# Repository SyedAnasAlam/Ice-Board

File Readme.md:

# Ice Board 
Ice Board is a FPGA development board containing the ICE40HX4k from Lattice.  
## Parts
- Lattice ICE40HX4K FPGA
- W25X20CL 2Mbit SPI Flash for storing configuration bitstream (104MHz)
- USB-C for configuring the FPGA using [IceBoard Programmer](https://github.com/SyedAnasAlam/IceBoard-Programmer) 
    - Also has option for programming the flash with a external device though breakout headers
- Requires 5V supply which can be supplied from either USB port or barrel jack (selectable with a header)
- FTDI4222 for USB to SPI conversion
- 64 x IO pins

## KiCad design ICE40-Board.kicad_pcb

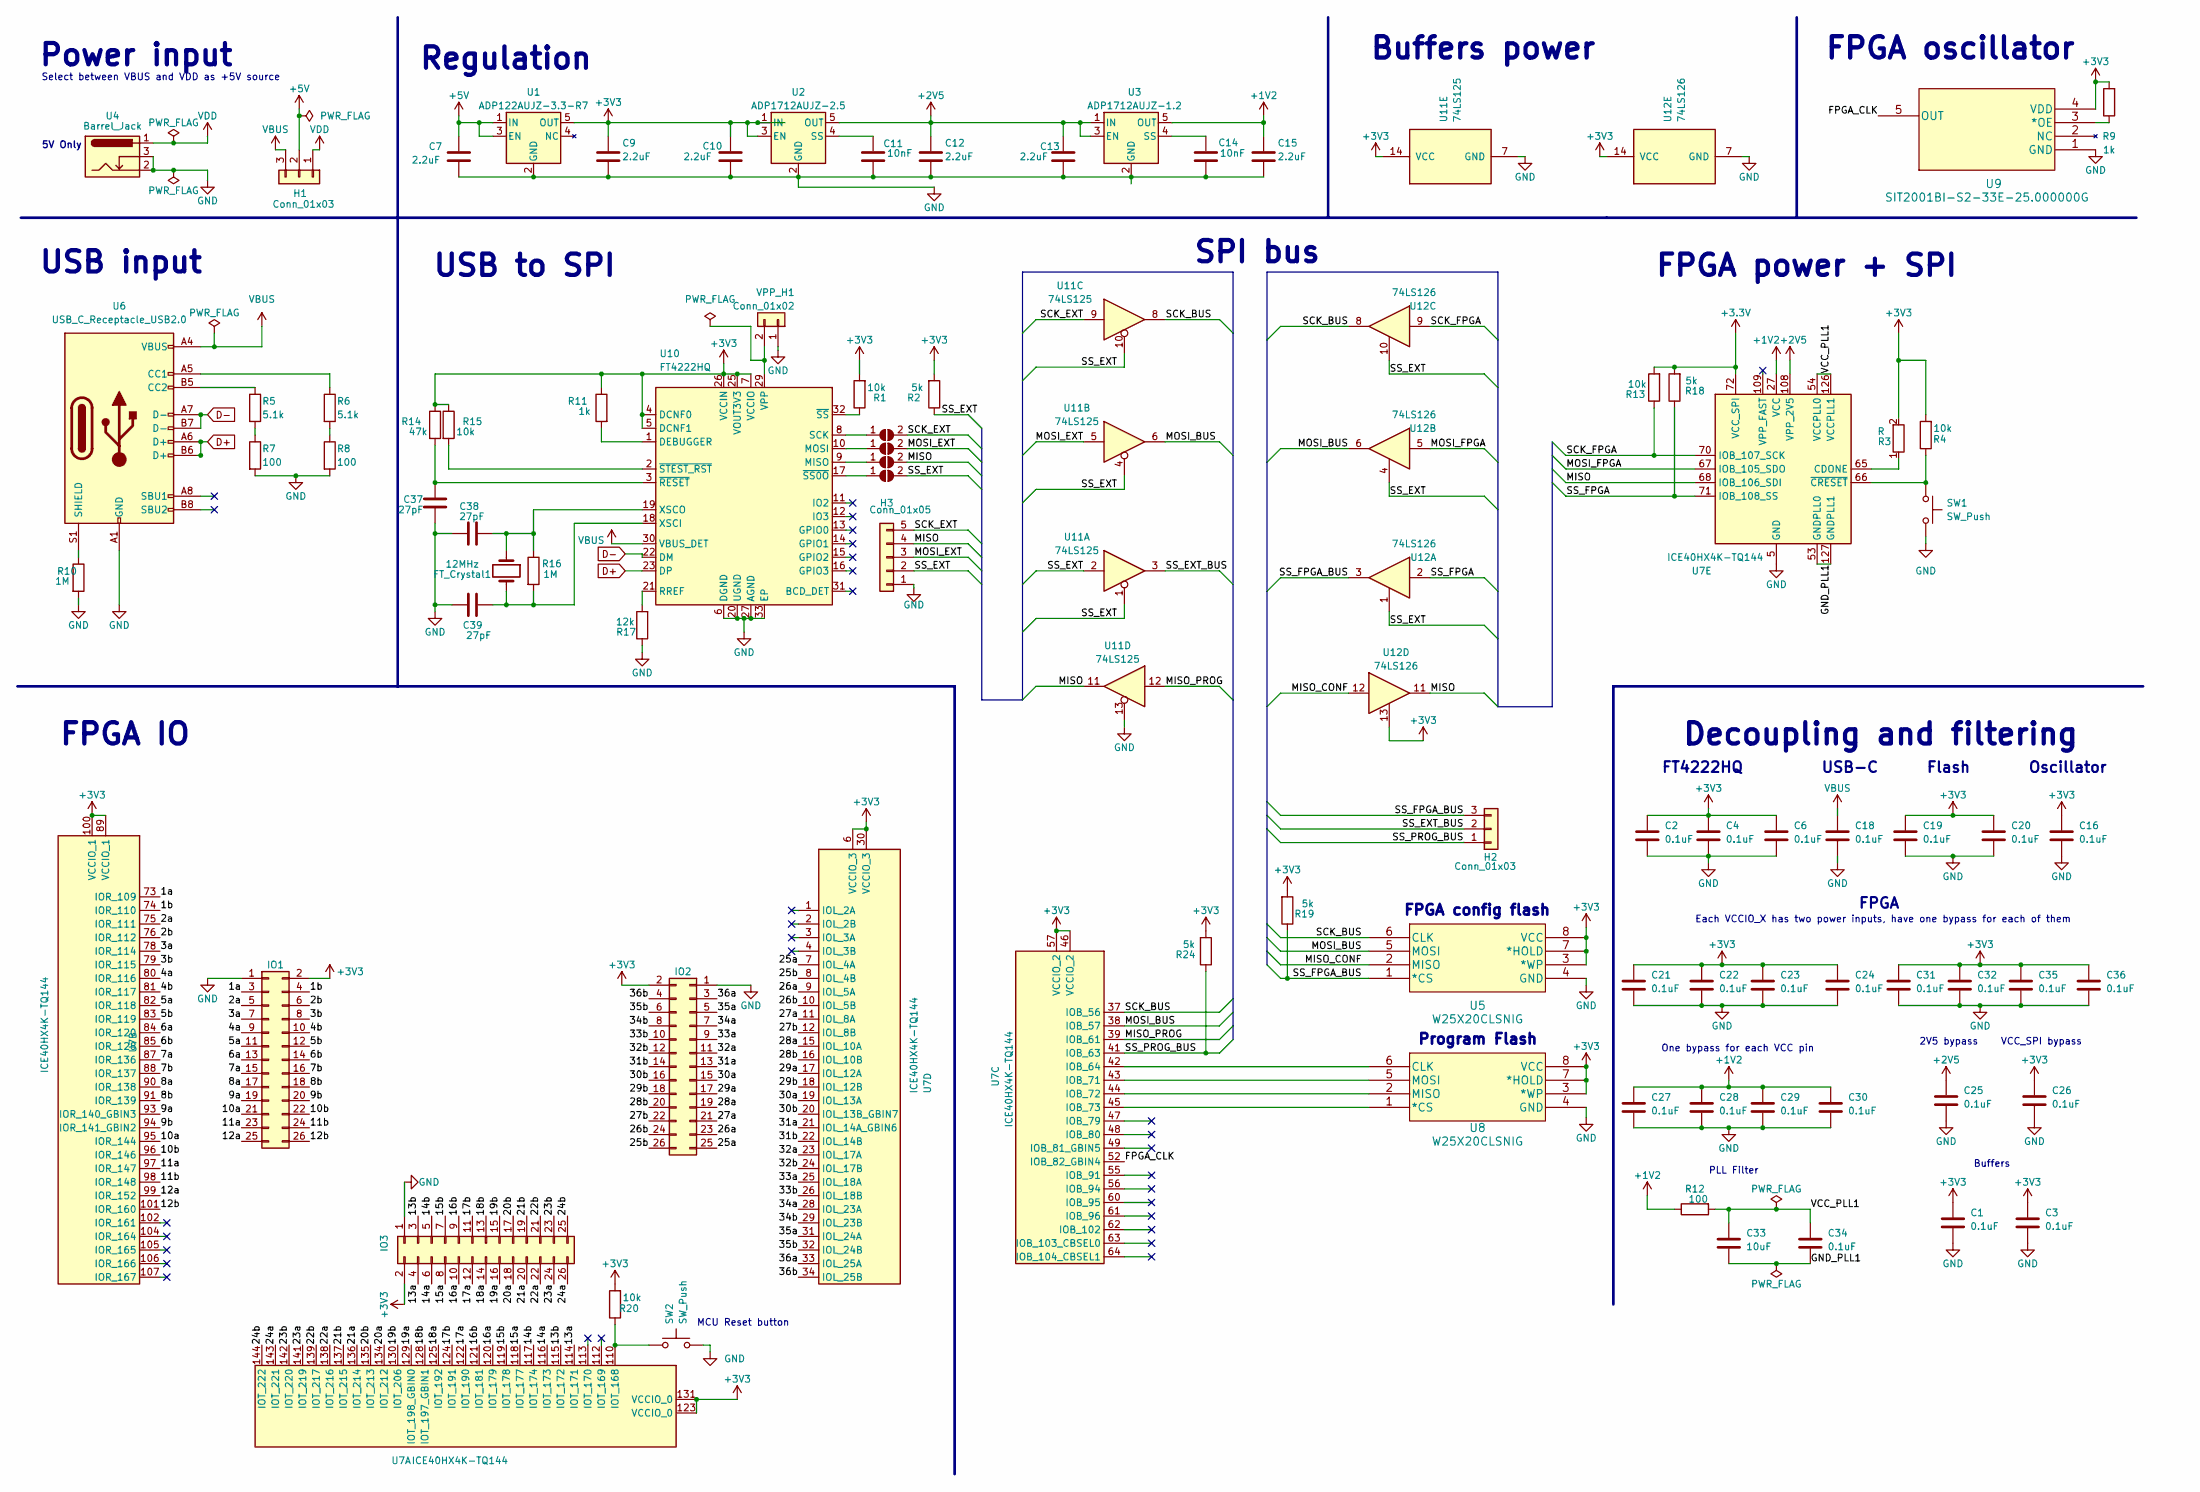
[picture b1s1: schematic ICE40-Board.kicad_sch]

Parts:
C1, C2, C3, C4, C6, C16, C18, C19, C20, C21, C22, C23, C24, C25, C26, C27, C28, C29, C30, C31, C32, C34, C35, C36: 0.1uF; C_0603_1608Metric_Pad1.08x0.95mm_HandSolder
C7, C9, C10, C12, C13, C15: 2.2uF; C_0603_1608Metric_Pad1.08x0.95mm_HandSolder
C11, C14: 10nF; C_0603_1608Metric_Pad1.08x0.95mm_HandSolder
C33: 10uF; C_0603_1608Metric_Pad1.08x0.95mm_HandSolder
C37, C38, C39: 27pF; C_0603_1608Metric_Pad1.08x0.95mm_HandSolder
FT_Crystal1: 12MHz; Crystal_HC49-U_Vertical
H1, H2: Conn_01x03; PinHeader_1x03_P2.54mm_Vertical
H3: Conn_01x05; PinHeader_1x05_P2.54mm_Vertical
IO1, IO2: Conn_02x13_Row_Letter_Last; PinHeader_2x13_P2.54mm_Vertical
IO3: Conn_02x09_Row_Letter_Last; PinHeader_2x13_P2.54mm_Vertical
JP2: SCK; SolderJumper-2_P1.3mm_Open_Pad1.0x1.5mm
JP3: MOSI; SolderJumper-2_P1.3mm_Open_Pad1.0x1.5mm
JP4: MISO; SolderJumper-2_P1.3mm_Open_Pad1.0x1.5mm
JP5: SS; SolderJumper-2_P1.3mm_Open_Pad1.0x1.5mm
R1, R4, R13, R15, R20: 10k; R_0603_1608Metric_Pad0.98x0.95mm_HandSolder
R2, R18, R19, R24: 5k; R_0603_1608Metric_Pad0.98x0.95mm_HandSolder
R3: R; R_0603_1608Metric_Pad0.98x0.95mm_HandSolder
R5, R6: 5.1k; R_0603_1608Metric_Pad0.98x0.95mm_HandSolder
R7, R8, R12: 100; R_0603_1608Metric_Pad0.98x0.95mm_HandSolder
R9, R11: 1k; R_0603_1608Metric_Pad0.98x0.95mm_HandSolder
R10, R16: 1M; R_0603_1608Metric_Pad0.98x0.95mm_HandSolder
R14: 47k; R_0603_1608Metric_Pad0.98x0.95mm_HandSolder
R17: 12k; R_0603_1608Metric_Pad0.98x0.95mm_HandSolder
SW1, SW2: SW_Push; SW_PUSH_6mm
U1: ADP122AUJZ-3.3-R7; SOT-23-5
U2: ADP1712AUJZ-2.5; SOT-23-5
U3: ADP1712AUJZ-1.2; SOT-23-5
U4: Barrel_Jack; CUI_PJ-007
U5, U8: W25X20CLSNIG; SOIC-8_3.9x4.9mm_P1.27mm
U6: USB_C_Receptacle_USB2.0; USB_C_Receptacle_Palconn_UTC16-G
U7: ICE40HX4K-TQ144; TQFP-144_20x20mm_P0.5mm
U9: SIT2001BI-S2-33E-25.000000G; SOT-23-5_HandSoldering
U10: FT4222HQ; VQFN-32-1EP_5x5mm_P0.5mm_EP3.1x3.1mm
U11: 74LS125; TSSOP-14_4.4x5mm_P0.65mm
U12: 74LS126; TSSOP-14_4.4x5mm_P0.65mm
VPP_H1: Conn_01x02; PinHeader_1x02_P2.54mm_Vertical

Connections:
+1V2: C15.1, C27.1, C28.1, C29.1, C30.1, R12.1, U3.5 (OUT), U7.27 (VCC), U7.40 (VCC), U7.92 (VCC), U7.111 (VCC)
+2V5: C12.1, C13.1, C25.1, U2.5 (OUT), U3.1 (IN), U3.3 (EN), U7.108 (VPP_2V5)
+5V: C7.1, H1.2, U1.1 (IN), U1.3 (EN)
/1a: IO1.3, U7.73 (IOR_109)
/1b: IO1.4, U7.74 (IOR_110)
/2a: IO1.5, U7.75 (IOR_111)
/2b: IO1.6, U7.76 (IOR_112)
/3a: IO1.7, U7.78 (IOR_114)
/3b: IO1.8, U7.79 (IOR_115)
/4a: IO1.9, U7.80 (IOR_116)
/4b: IO1.10, U7.81 (IOR_117)
/5a: IO1.11, U7.82 (IOR_118)
/5b: IO1.12, U7.83 (IOR_119)
/6a: IO1.13, U7.84 (IOR_120)
/6b: IO1.14, U7.85 (IOR_128)
/7a: IO1.15, U7.87 (IOR_136)
/7b: IO1.16, U7.88 (IOR_137)
/8a: IO1.17, U7.90 (IOR_138)
/8b: IO1.18, U7.91 (IOR_139)
/9a: IO1.19, U7.93 (IOR_140_GBIN3)
/9b: IO1.20, U7.94 (IOR_141_GBIN2)
/10a: IO1.21, U7.95 (IOR_144)
/10b: IO1.22, U7.96 (IOR_146)
/11a: IO1.23, U7.97 (IOR_147)
/11b: IO1.24, U7.98 (IOR_148)
/12a: IO1.25, U7.99 (IOR_152)
/12b: IO1.26, U7.101 (IOR_160)
/13a: IO3.4, U7.114 (IOT_171)
/13b: IO3.3, U7.115 (IOT_172)
/14a: IO3.6, U7.116 (IOT_173)
/14b: IO3.5, U7.117 (IOT_174)
/15a: IO3.8, U7.118 (IOT_177)
/15b: IO3.7, U7.119 (IOT_178)
/16a: IO3.10, U7.120 (IOT_179)
/16b: IO3.9, U7.121 (IOT_181)
/17a: IO3.12, U7.122 (IOT_190)
/17b: IO3.11, U7.124 (IOT_191)
/18a: IO3.14, U7.125 (IOT_192)
/18b: IO3.13, U7.128 (IOT_197_GBIN1)
/19a: IO3.16, U7.129 (IOT_198_GBIN0)
/19b: IO3.15, U7.130 (IOT_206)
/20a: IO3.18, U7.134 (IOT_212)
/20b: IO3.17, U7.135 (IOT_213)
/21a: IO3.20, U7.136 (IOT_214)
/21b: IO3.19, U7.137 (IOT_215)
/22a: IO3.22, U7.138 (IOT_216)
/22b: IO3.21, U7.139 (IOT_217)
/23a: IO3.24, U7.141 (IOT_219)
/23b: IO3.23, U7.142 (IOT_220)
/24a: IO3.26, U7.143 (IOT_221)
/24b: IO3.25, U7.144 (IOT_222)
/25a: IO2.25, U7.7 (IOL_4A)
/25b: IO2.26, U7.8 (IOL_4B)
/26a: IO2.23, U7.9 (IOL_5A)
/26b: IO2.24, U7.10 (IOL_5B)
/27a: IO2.21, U7.11 (IOL_8A)
/27b: IO2.22, U7.12 (IOL_8B)
/28a: IO2.19, U7.15 (IOL_10A)
/28b: IO2.20, U7.16 (IOL_10B)
/29a: IO2.17, U7.17 (IOL_12A)
/29b: IO2.18, U7.18 (IOL_12B)
/30a: IO2.15, U7.19 (IOL_13A)
/30b: IO2.16, U7.20 (IOL_13B_GBIN7)
/31a: IO2.13, U7.21 (IOL_14A_GBIN6)
/31b: IO2.14, U7.22 (IOL_14B)
/32a: IO2.11, U7.23 (IOL_17A)
/32b: IO2.12, U7.24 (IOL_17B)
/33a: IO2.9, U7.25 (IOL_18A)
/33b: IO2.10, U7.26 (IOL_18B)
/34a: IO2.7, U7.28 (IOL_23A)
/34b: IO2.8, U7.29 (IOL_23B)
/35a: IO2.5, U7.31 (IOL_24A)
/35b: IO2.6, U7.32 (IOL_24B)
/36a: IO2.3, U7.33 (IOL_25A)
/36b: IO2.4, U7.34 (IOL_25B)
/FPGA_CLK: U7.52 (IOB_82_GBIN4), U9.5 (OUT)
/GND_PLL1: C33.2, C34.2, U7.53 (GNDPLL0), U7.127 (GNDPLL1)
/MISO: H3.4, JP4.2 (B), U7.68 (IOB_106_SDI), U11.11, U12.11
/MISO_CONF: U5.2 (MISO), U12.12
/MISO_PROG: U7.39 (IOB_61), U11.12
/MOSI_BUS: U5.5 (MOSI), U7.38 (IOB_57), U11.6, U12.6
/MOSI_EXT: H3.3, JP3.2 (B), U11.5
/MOSI_FPGA: U7.67 (IOB_105_SDO), U12.5
/SCK_BUS: U5.6 (CLK), U7.37 (IOB_56), U11.8, U12.8
/SCK_EXT: H3.5, JP2.2 (B), U11.9
/SCK_FPGA: R13.1, U7.70 (IOB_107_SCK), U12.9
/SS_EXT: H3.2, JP5.2 (B), R2.1, U11.1, U11.2, U11.4, U11.10, U12.1, U12.4, U12.10
/SS_EXT_BUS: H2.2, U11.3
/SS_FPGA: R18.1, U7.71 (IOB_108_SS), U12.2
/SS_FPGA_BUS: H2.3, R19.1, U5.1 (*CS), U12.3
/SS_PROG_BUS: H2.1, R24.1, U7.41 (IOB_63)
/VCC_PLL1: C33.1, C34.1, R12.2, U7.54 (VCCPLL0), U7.126 (VCCPLL1)
D+: U6.A6 (D+), U6.B6 (D+), U10.23 (DP)
D-: U6.A7 (D-), U6.B7 (D-), U10.22 (DM)
GND: C1.2, C2.2, C3.2, C4.2, C6.2, C7.2, C9.2, C10.2, C11.2, C12.2, C13.2, C14.2, C15.2, C16.2, C18.2, C19.2, C20.2, C21.2, C22.2, C23.2, C24.2, C25.2, C26.2, C27.2, C28.2, C29.2, C30.2, C31.2, C32.2, C35.2, C36.2, C37.1, C38.2, C39.2, H3.1, IO1.1, IO2.1, IO3.1, R7.2, R8.2, R10.2, R17.1, SW1.2, SW2.2, U1.2 (GND), U2.2 (GND), U3.2 (GND), U4.2, U4.3, U5.4 (GND), U6.A1 (GND), U6.A12 (GND), U6.B1 (GND), U6.B12 (GND), U7.5 (GND), U7.13 (GND), U7.14 (GND), U7.59 (GND), U7.69 (GND), U7.86 (GND), U7.103 (GND), U7.132 (GND), U7.140 (GND), U8.4 (GND), U9.1 (GND), U10.6 (DGND), U10.20 (UGND), U10.24 (UGND), U10.27 (AGND), U10.28 (DGND), U10.33 (EP), U11.7 (GND), U11.13, U12.7 (GND), VPP_H1.1
unnamed: C11.1, U2.4 (SS)
unnamed: C14.1, U3.4 (SS)
unnamed: C37.2, R14.2, U10.3 (~RESET)
unnamed: C38.1, FT_Crystal1.1, R16.1, U10.19 (XSCO)
unnamed: C39.1, FT_Crystal1.2, R16.2, U10.18 (XSCI)
unnamed: JP2.1 (A), U10.8 (SCK)
unnamed: JP3.1 (A), U10.10 (MOSI)
unnamed: JP4.1 (A), U10.9 (MISO)
unnamed: JP5.1 (A), U10.17 (~SS0O)
unnamed: R1.1, U10.32 (~SS)
unnamed: R3.1, U7.65 (CDONE)
unnamed: R4.1, SW1.1, U7.66 (~CRESET)
unnamed: R5.1, U6.B5 (CC2)
unnamed: R5.2, R7.1
unnamed: R6.1, U6.A5 (CC1)
unnamed: R6.2, R8.1
unnamed: R9.1, U9.3 (*OE)
unnamed: R10.1, U6.S1 (SHIELD)
unnamed: R11.2, U10.1 (DEBUGGER)
unnamed: R15.2, U10.2 (~STEST_RST)
unnamed: R17.2, U10.21 (RREF)
unnamed: R20.1, SW2.1, U7.110 (IOT_168)
unnamed: U7.42 (IOB_64), U8.6 (CLK)
unnamed: U7.43 (IOB_71), U8.5 (MOSI)
unnamed: U7.44 (IOB_72), U8.2 (MISO)
unnamed: U7.45 (IOB_73), U8.1 (*CS)
unnamed: U10.29 (VPP), VPP_H1.2
VBUS: C18.1, H1.3, U6.A4 (VBUS), U6.A9 (VBUS), U6.B4 (VBUS), U6.B9 (VBUS), U10.30 (VBUS_DET)
VDD: H1.1, U4.1

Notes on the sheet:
Regulation
MCU Reset button
USB-C
Program Flash
USB to SPI
FT4222HQ
Select between VBUS and VDD as +5V source
SPI bus
USB input
Flash
Buffers power
Buffers
FPGA oscillator
5V Only
Oscillator
FPGA power + SPI
One bypass for each VCC pin
FPGA config flash
PLL Filter
VCC_SPI bypass
Decoupling and filtering
Power input
FPGA IO
2V5 bypass
FPGA
Each VCCIO_X has two power inputs, have one bypass for each of them

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
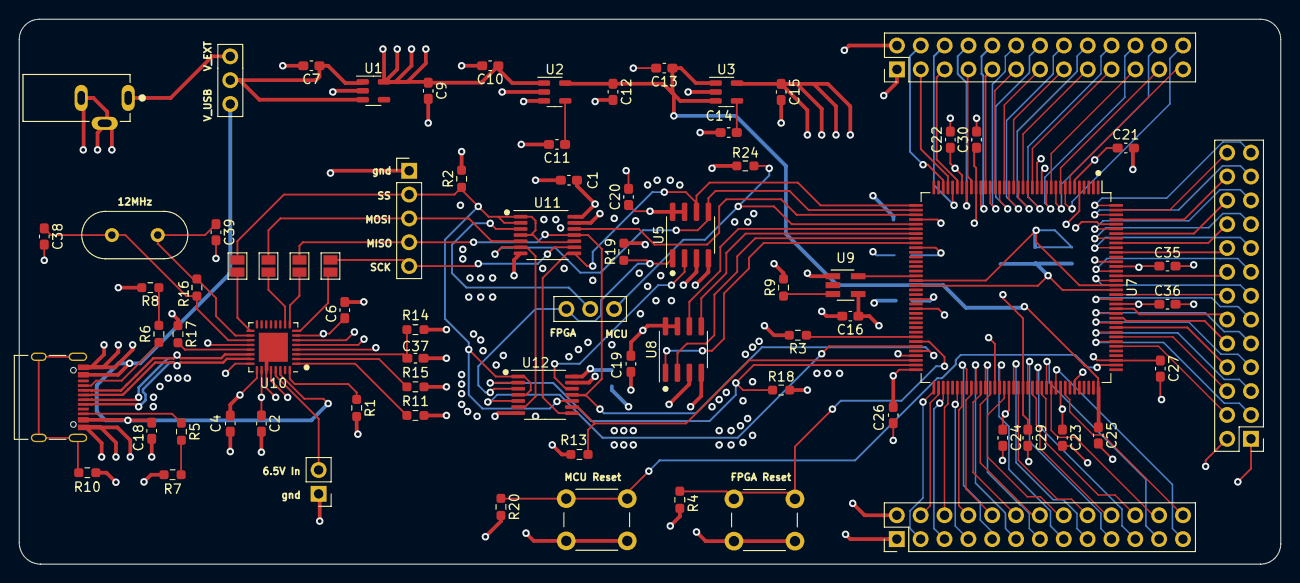
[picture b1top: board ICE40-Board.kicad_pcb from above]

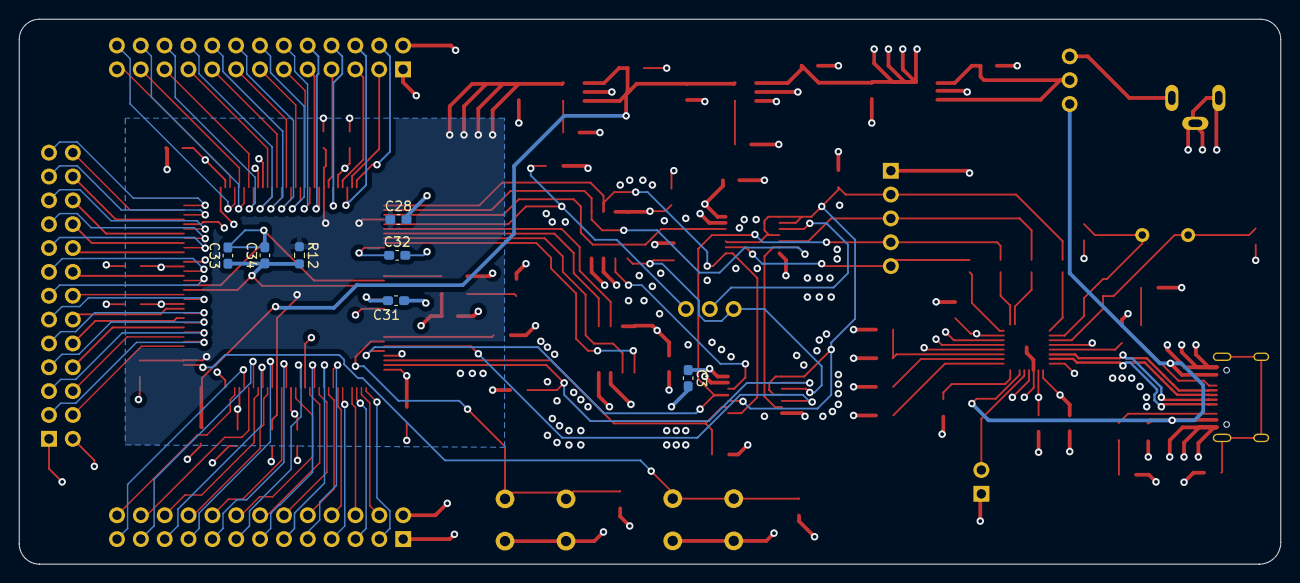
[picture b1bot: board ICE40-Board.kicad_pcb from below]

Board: 4 copper layers, 134.4 x 58.0 mm, 83 parts (7 on the bottom side), 125 nets.

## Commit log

2022-03-02 First revision of schematic layout, no errors in ERC
2022-03-02 Starting routing
2022-03-02 Changed reference designation method to simple letter + number
2022-03-02 Begun initial routing with simple reference designation
2022-03-03 Committing before changing footprints to hand solder version for resistors and capacitors
2022-03-05 Initial routing
2022-03-06 USB-C routing complete
2022-03-08 Routing buffers and flash
2022-03-09 Allowing MISO for both config and program flash when programming
2022-03-09 everything routed just IO pins remaining
2022-03-09 previous commit message incorrect, this commit has fully routed design except IO
2022-03-09 No DRC errors, board fully routed
2022-03-09 Minor changed
2022-03-10 Adjusted component and track clearances
2022-03-10 Impedance controlled USB routing
2022-03-10 Added ground vias for better signal integrity, added silkscreen text, added reset button for MCU
2022-03-10 Added dimension
2022-03-10 Placed vias around SPI lines, placed main oscillator closer to FPGA
2022-03-15 Version 1.0 completed
